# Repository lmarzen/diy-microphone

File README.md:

# diy-microphone

This project contributes a KiCad PCB design that implements the circuit described in the DIY Perks Microphone Project v1, https://www.youtube.com/watch?v=LoQu3XXIayc.

The PCB is designed to fit the internal form factor of the body of BM-800 XLR microphone. The BM-800 is an inexpensive microphone with a metal housing. The limited interior space of the microphone housing necessitates a dense PCB layout.

The XLR plug is replaced with a USB C female connector and a 3d printed mount is used to secure it. The SolidWorks part file and the .STL have been included as part of this repository. Additionally this 3d printable mount is used to hold the mic capsole, https://www.thingiverse.com/thing:2541735. I used a 1k reverse log potentiometer for volume control. It works and sounds great! Here are some pictures.

Matt (DIY Perks) has created extensive documentation for the DIY Perks Microphone Project v1 in the form of a youtube video, https://www.youtube.com/watch?v=LoQu3XXIayc. More information related to his project can be found here, https://diyperks.com/project_31_high-quality-usb-c-microphone/.

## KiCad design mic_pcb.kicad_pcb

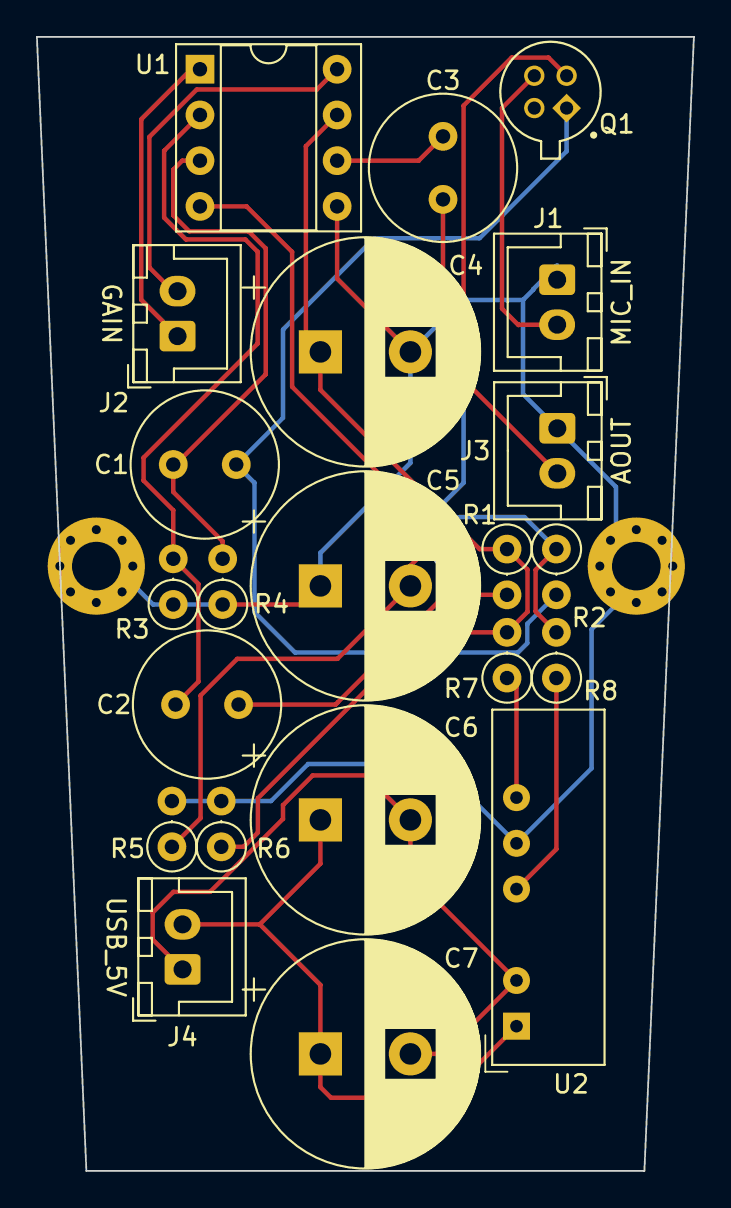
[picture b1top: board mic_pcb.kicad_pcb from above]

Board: 2 copper layers, 36.5 x 63.0 mm, 22 parts (0 on the bottom side), 16 nets.

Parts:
C1, C2, C3: 22uf 35v; C_Radial_D8.0mm_H11.5mm_P3.50mm
C4, C5, C6, C7: 2200uf 16v; CP_Radial_D12.5mm_P5.00mm
J1: MIC_IN; JST_XH_B2B-XH-A_1x02_P2.50mm_Vertical
J2: GAIN; JST_XH_B2B-XH-A_1x02_P2.50mm_Vertical
J3: AUDIO_OUT; JST_XH_B2B-XH-A_1x02_P2.50mm_Vertical
J4: 5v USB; JST_XH_B2B-XH-A_1x02_P2.50mm_Vertical
Q1: 2N4416; TO127P584H533-4
R1, R2, R5, R6: 2.2k; R_Axial_DIN0207_L6.3mm_D2.5mm_P2.54mm_Vertical
R3, R4: 3.9k; R_Axial_DIN0207_L6.3mm_D2.5mm_P2.54mm_Vertical
R7, R8: 100; R_Axial_DIN0207_L6.3mm_D2.5mm_P2.54mm_Vertical
U1: THAT1512; DIP-8_W7.62mm_Socket
U2: NMA0515SC; Converter_DCDC_Murata_NMAxxxxSC_THT

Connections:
GNDREF: C4.2, C5.1, J1.1, J3.1, R3.1, R4.1, R5.2, R6.2, U1.5 (REF), U2.5 (0V)
unnamed: C1.1, R4.2, U1.3 (IN+)
unnamed: C1.2, Q1.1, R2.2
unnamed: C2.1, R3.2, U1.2 (IN-)
unnamed: C2.2, Q1.2, R1.2
unnamed: C3.1, J3.2
unnamed: C3.2, U1.6
unnamed: C4.1, R1.1, R6.1, R7.2, U1.7 (V+)
unnamed: C5.2, R2.1, R5.1, R8.2, U1.4 (V-)
unnamed: C6.1, C7.1, J4.2, U2.1 (VIN+)
unnamed: C6.2, C7.2, J4.1, U2.2 (VIN-)
unnamed: J1.2, Q1.3
unnamed: J2.1, U1.1 (RG1)
unnamed: J2.2, U1.8 (RG2)
unnamed: R7.1, U2.6 (VOUT+)
unnamed: R8.1, U2.4 (VOUT-)

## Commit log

2023-02-19 updated .gitignore
2023-02-19 added kicad files
2023-02-19 added 3d model files
2023-02-19 added images
2023-02-19 rotated image
2023-02-19 updated pcb image
